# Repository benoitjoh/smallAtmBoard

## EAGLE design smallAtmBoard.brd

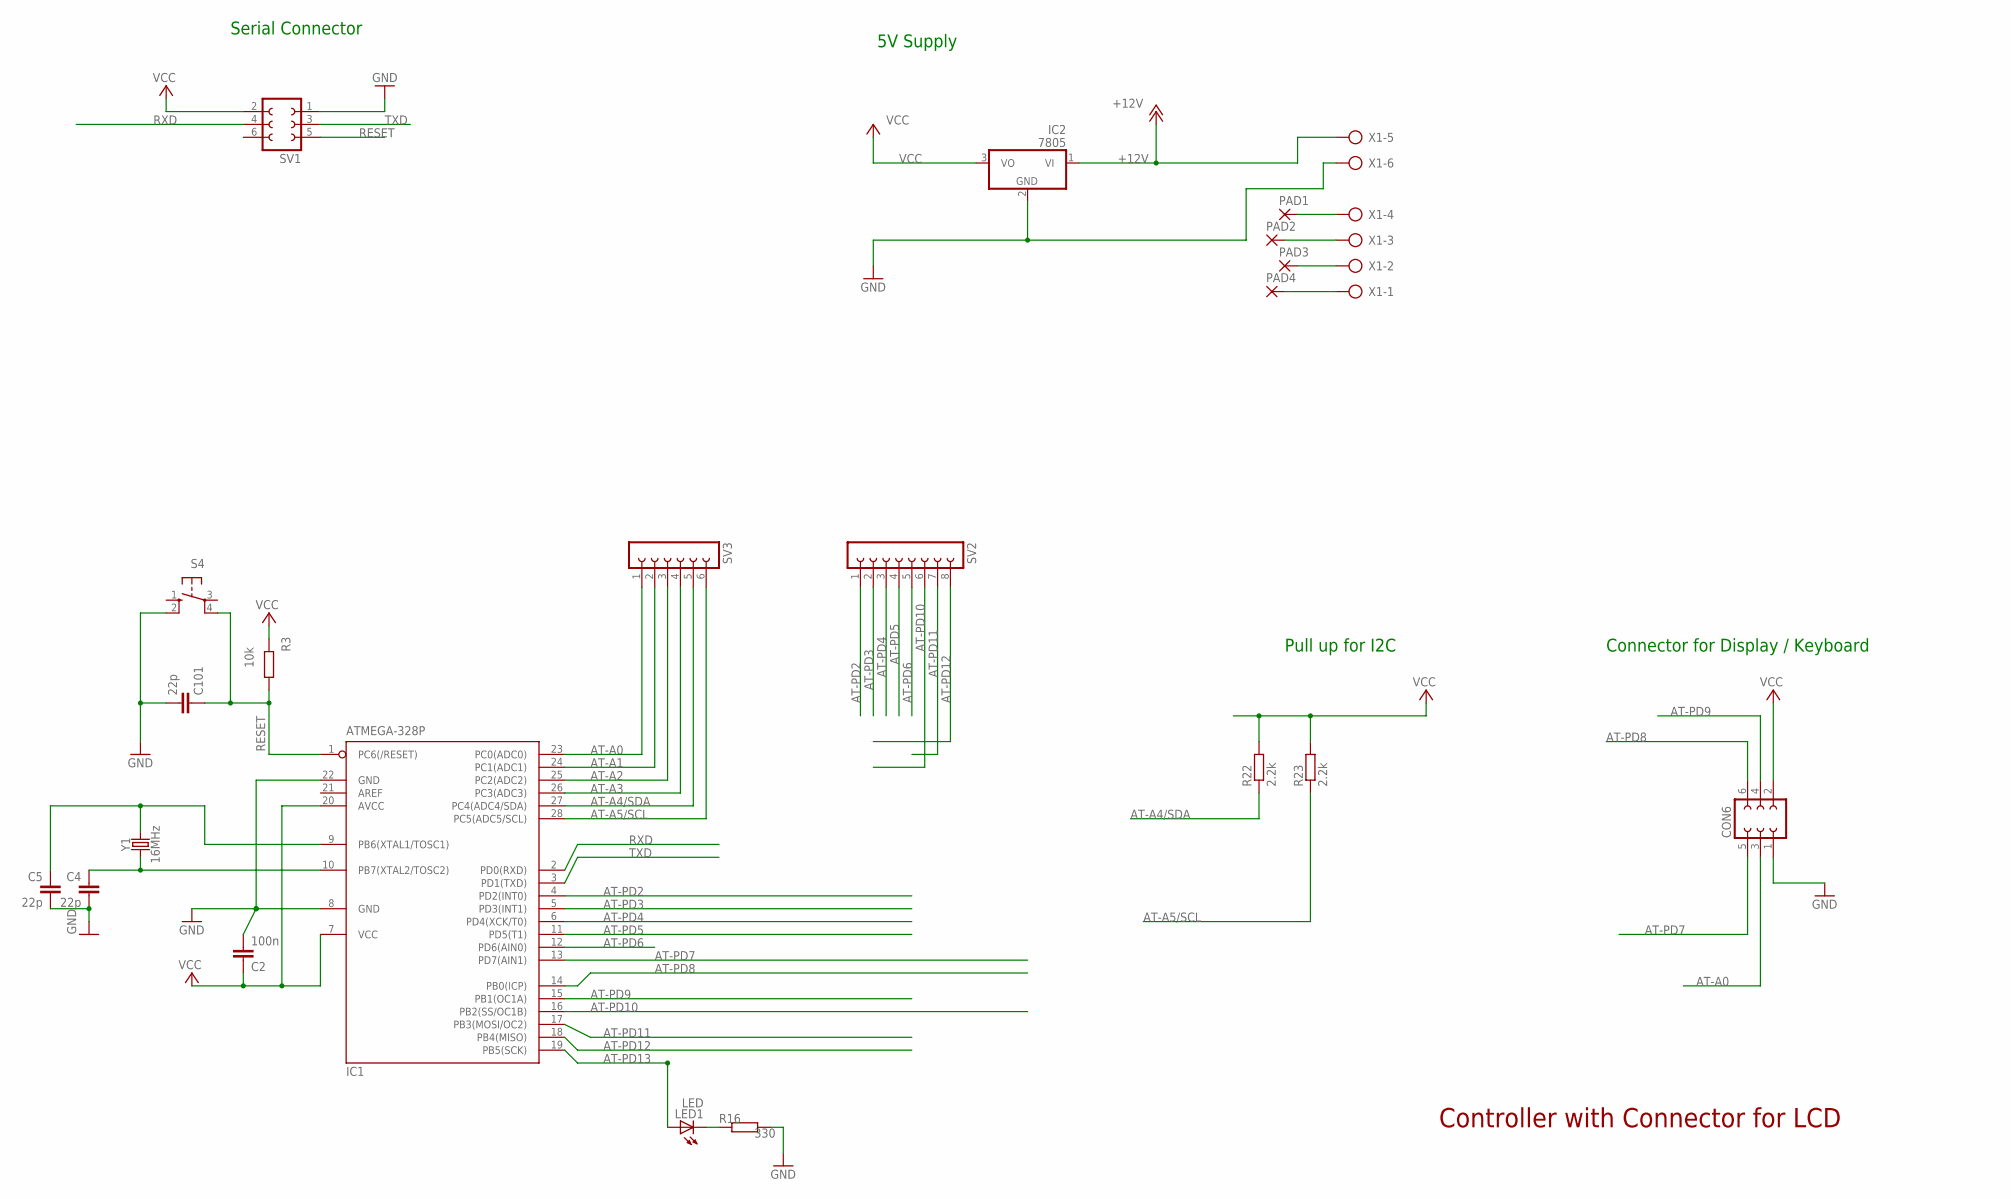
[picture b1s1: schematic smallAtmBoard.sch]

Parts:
C2: 100n; C050-024X044
C4, C5, C101: 22p; C050-024X044
CON6: FE03-2
IC1: ATMEGA-328P; DIL28-3
IC2: 7805; TO220V
LED1: LED; LED_LD260
PAD1, PAD2, PAD3, PAD4: PAD1,6/0,8
R3: 10k; R_0207/2V
R16: 330; R_0207/2V
R22, R23: 2.2k; R_0207/2V
S4: 10-XX; B3F-10XX
SV1: FE03-2FE03-2RAW; FE03-2RAW
SV2: FE08-1FE08-RAW; FE08-1-RAW
SV3: FE06-1FE06-1-RAW; FE06-1-RAW
X1: AK300/6
Y1: 16MHz; HC49US

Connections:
+12V: IC2.1 (VI), X1.5
AT-A0: CON6.3, IC1.23 (PC0(ADC0)), SV3.1
AT-A1: IC1.24 (PC1(ADC1)), SV3.2
AT-A2: IC1.25 (PC2(ADC2)), SV3.3
AT-A3: IC1.26 (PC3(ADC3)), SV3.4
AT-A4/SDA: IC1.27 (PC4(ADC4/SDA)), R22.1, SV3.5
AT-A5/SCL: IC1.28 (PC5(ADC5/SCL)), R23.1, SV3.6
AT-PD2: IC1.4 (PD2(INT0)), SV2.1
AT-PD3: IC1.5 (PD3(INT1)), SV2.2
AT-PD4: IC1.6 (PD4(XCK/T0)), SV2.3
AT-PD5: IC1.11 (PD5(T1)), SV2.4
AT-PD6: IC1.12 (PD6(AIN0)), SV2.5
AT-PD7: CON6.5, IC1.13 (PD7(AIN1))
AT-PD8: CON6.6, IC1.14 (PB0(ICP))
AT-PD9: CON6.4, IC1.15 (PB1(OC1A))
AT-PD10: IC1.16 (PB2(SS/OC1B)), SV2.6
AT-PD11: IC1.17 (PB3(MOSI/OC2)), SV2.7
AT-PD12: IC1.18 (PB4(MISO)), SV2.8
AT-PD13: IC1.19 (PB5(SCK)), LED1.A
GND: C2.2, C4.2, C5.2, C101.2, CON6.1, IC1.8 (GND), IC1.22 (GND), IC2.2 (GND), R16.1, S4.2 (S1), SV1.1, X1.6
unnamed: LED1.K (C), R16.2
unnamed: PAD1.1, X1.4
unnamed: PAD2.1, X1.3
unnamed: PAD3.1, X1.2
unnamed: PAD4.1, X1.1
RESET: C101.1, IC1.1 (PC6(/RESET)), R3.2, S4.4 (P1), SV1.5
RXD: IC1.2 (PD0(RXD)), SV1.4
TXD: IC1.3 (PD1(TXD)), SV1.3
VCC: C2.1, CON6.2, IC1.7 (VCC), IC1.20 (AVCC), IC2.3 (VO), R3.1, R22.2, R23.2, SV1.2
XTAL1: C5.1, IC1.9 (PB6(XTAL1/TOSC1)), Y1.2
XTAL2: C4.1, IC1.10 (PB7(XTAL2/TOSC2)), Y1.1

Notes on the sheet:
Controller with Connector for LCD
Serial Connector
5V Supply
Connector for Display / Keyboard
Pull up for I2C

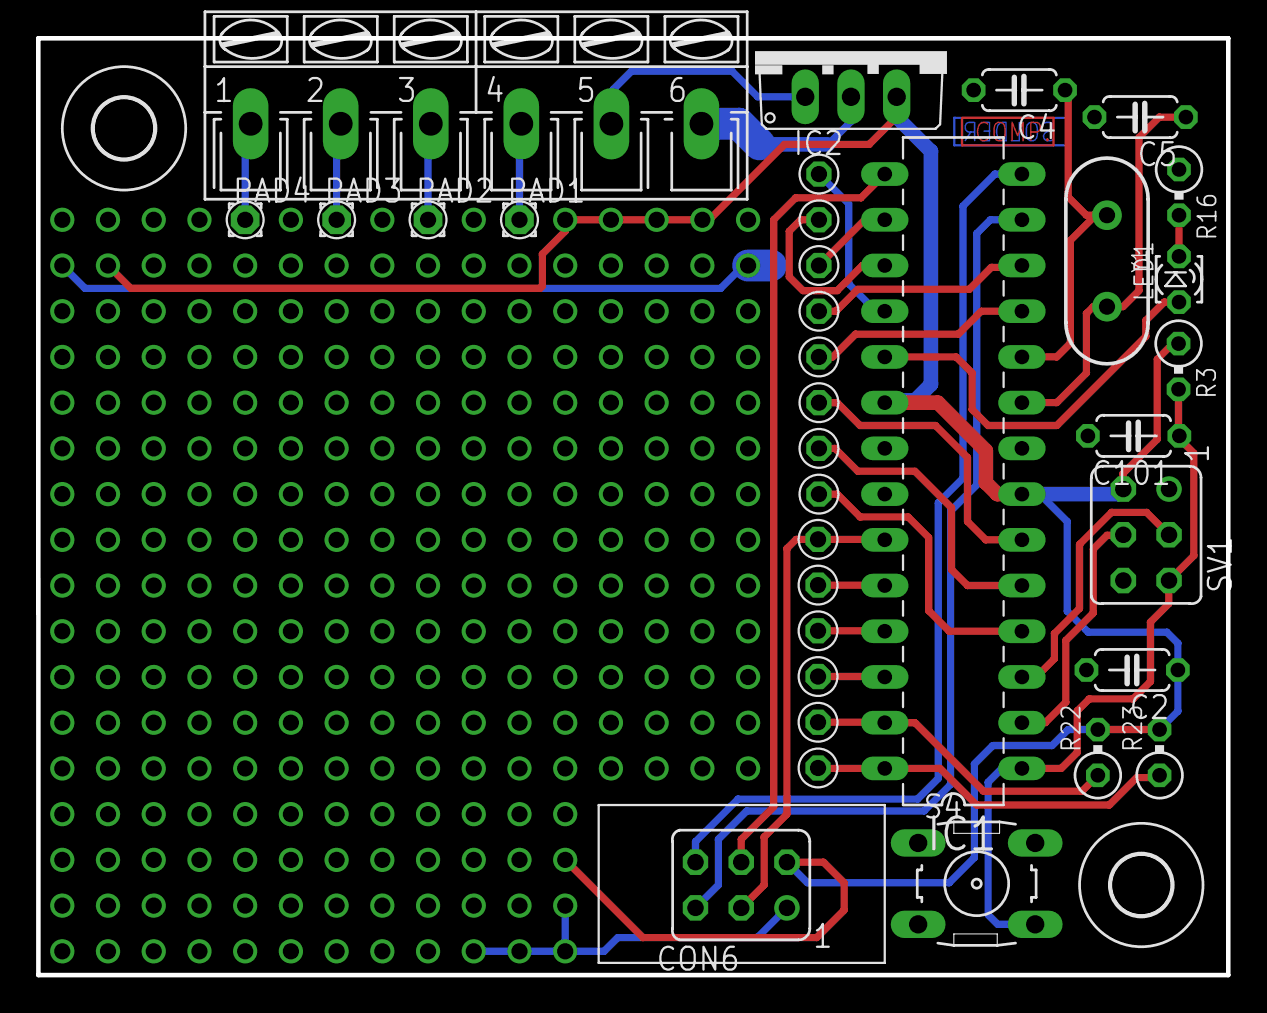
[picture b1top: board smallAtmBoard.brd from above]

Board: 2 copper layers, 66.1 x 52.0 mm, 26 parts (0 on the bottom side), 31 nets.

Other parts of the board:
U$1, U$3: 3,3
U$6: SOLDER
U$7: COMP

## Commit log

2018-10-26 connector and routing
2018-10-26 route
2018-10-28 finish routing
2018-10-28 rename files
2018-10-30 Idioten schriftzug
2018-11-06 docu, finetuning
2018-11-11 fix grid and value positioning
2018-12-17 new connectors + routing
2019-01-06 adjust to new system and gerbmerge
2019-01-07 move gerbv projects files to eagletools, unify holes diameter
2019-01-07 reduce number of drilltools
2019-01-09 smaller header
2019-01-09 standartize pins on LCD connector
2019-01-14 move 7805 and change connector
2019-01-16 remove usb connector. nees too much space
2019-01-21 remove i2c socket
2019-01-29 turn around connector for lcd and kbd
2019-01-29 correct labels
2019-10-25 exchange D10 and D12, no i2c
